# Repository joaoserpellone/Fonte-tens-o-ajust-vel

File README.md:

# Fonte de Tensão ajustável 
# Diagrama do circuito

[Link para o circuito no falstad](https://tinyurl.com/29xfh3vj)

# Link para vídeo da apresentação
https://youtube.com/shorts/_ifSP6hrwoE

# Lista de compontentes:
  * Transformador: componente que é utilizado para reduzir a corrente vinda da tomada (127v em média) para valores mais baixos, em torno de 24v.
  * Ponte de diodo: utilizando-se 4 diodos (1N4007), fizemos um "cruzamento entre eles". Isso é necessário para mudar a fase negativa da corrente alternada e torná-la sempre positiva.
  * Capacitor: acumula tensão na fase de aumento da tensão interna do circuito e, na fase de diminuição libera a ddp acumulada para o circuito.
  * Resistor: há três resistores utilizados no circuito, o primeiro de 2k (no circuito real ligamos dois de 1k em série) para reduzir a corrente que passa pelo led, o segundo de 1k após o capacitor, que reduz a tensão vinda de aproximadamente 24v para em torno de 13v. O segundo, de 3.5k (que, na prática, utilizamos dois de 5k em paralelo e um de 1k em série, resultando nos 3.5k desejados), se faz necessário para reduzir a corrente para 100mA na parte do componente a ser alimentado.
  * Diodo Zenner: regula a tensão máxima, caso a tensão vinda seja maior que a tensão do diodo, ele permite e apassagem de corrente e diminui até os 12v desejados, no nosso caso utilizamos o de 13v no circuito prático.
  * Potenciometro: dispositivo que permite mudar a resistência interna dele mesmo e consequentemente ajustar a tensão entre 12v (máximo) e 3v (mínimo).
  * Transistor: permite a passagem de corrente desejada (100ma) anterior ao potenciometro.

## Componentes escolhidos:

| Qtd | Componente       | Preço  |
| --- |:----------------:| ------:|
| 4   | Diodo 1N4007     | R$ 0,20|
| 1   | Capacitor 470uF  | R$ 1,05|
| 3   | Resistor 1k      | R$ 0,21|
| 2   | Resistor 5k      | R$ 0,14|
| 1   | Diodo Zenner(13v)| R$ 0,50|
| 1   | Potenciometro 10k| R$ 4,75|
| 1   | Tranistor 2N3904 | R$ 0,40|
| Total|                 | R$ 7,20|

# Circuito esquemático no EAGLE

# Participantes 

João Pedro Oliveira Serpellone - 13671848
Vinícius Carneiro Macedo - 11915752 

# Circuito PCB no EAGLE

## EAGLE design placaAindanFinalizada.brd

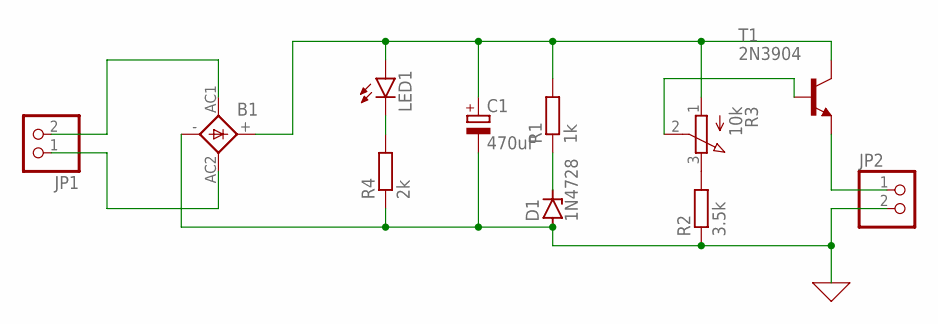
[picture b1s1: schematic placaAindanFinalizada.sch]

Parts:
B1: 1KAB
C1: 470uF; E5-10,5
D1: 1N4728; DO41Z10
JP1, JP2: PINHD-1X2; 1X02
LED1: LED5MM
R1: 1k; 0204/7
R2: 3.5k; 0204/7
R3: 10k; 3RP/1610N
R4: 2k; 0204/7
T1: 2N3904; TO92

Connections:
0: B1.-, C1.-, D1.A, JP2.2, R2.1, R4.1
unnamed: B1.AC1, JP1.2
unnamed: B1.AC2, JP1.1
unnamed: B1.+, C1.+, LED1.A, R1.2, R3.1 (A), T1.1 (C)
unnamed: R2.2, R3.3 (E)
unnamed: JP2.1, T1.3 (E)
unnamed: D1.C, R1.1
unnamed: LED1.K (C), R4.2
unnamed: R3.2 (S), T1.2 (B)

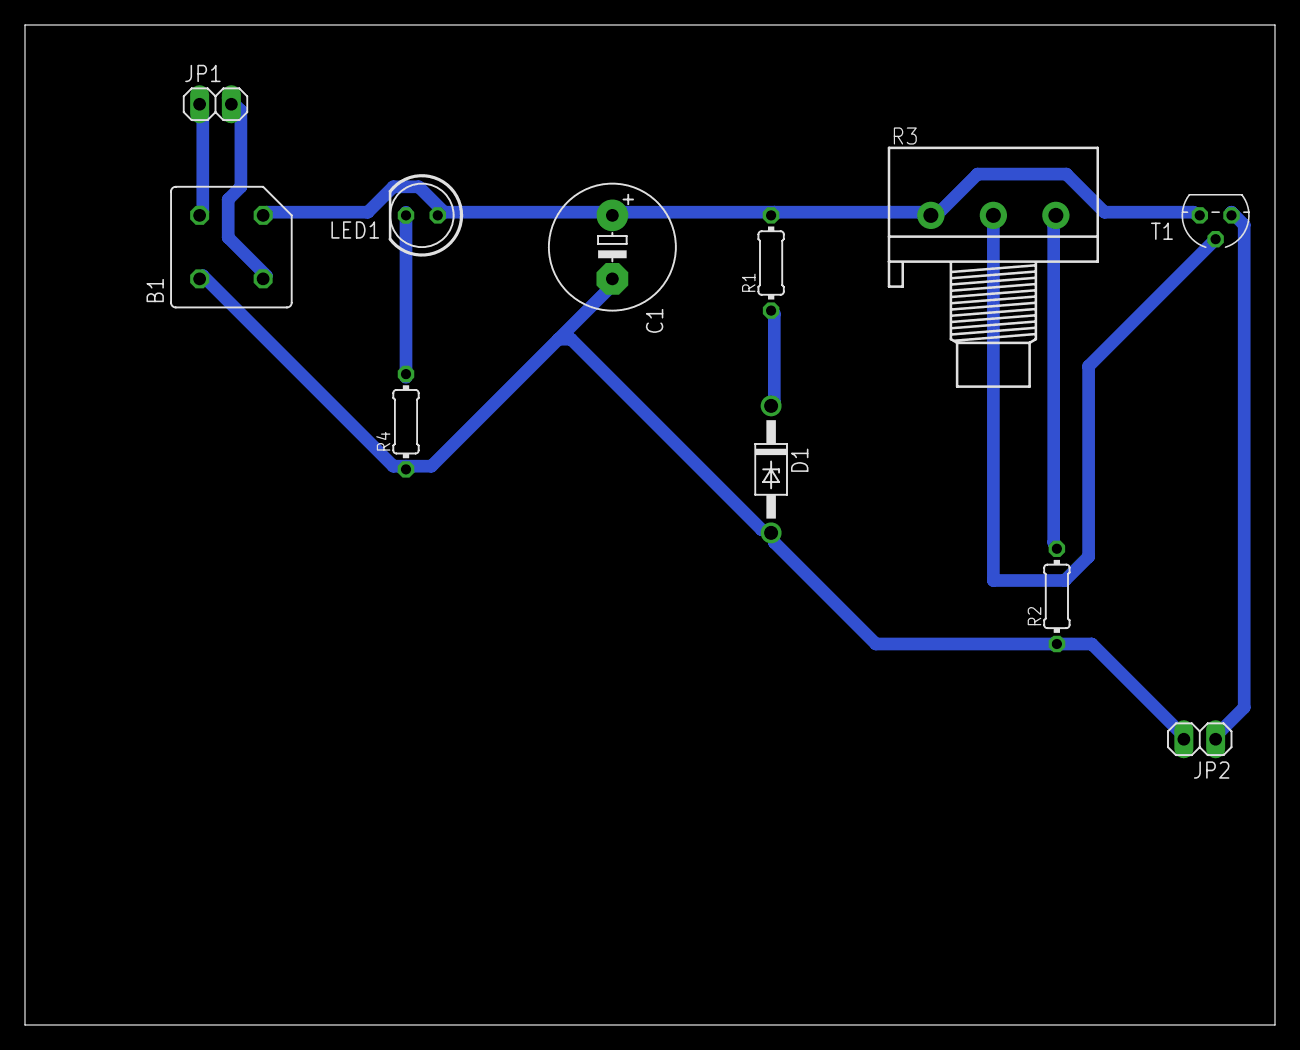
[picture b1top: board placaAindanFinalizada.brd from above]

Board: 2 copper layers, 100.0 x 80.0 mm, 11 parts (0 on the bottom side), 9 nets.
